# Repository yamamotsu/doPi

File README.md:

# doPi

"doPi" is Simple Raspberry Pi zero DAC Board.

## Feature

- DAC: PCM5102 by Texas Instruments
  - Sampling Rate: 384kHz Max(using up to 192kHz)
  - Number of bits of sample: 32-Bit
- Output: 3.5mm 3-pole jack
- Function: Next,Prev,Play/Stop, Volume +/-

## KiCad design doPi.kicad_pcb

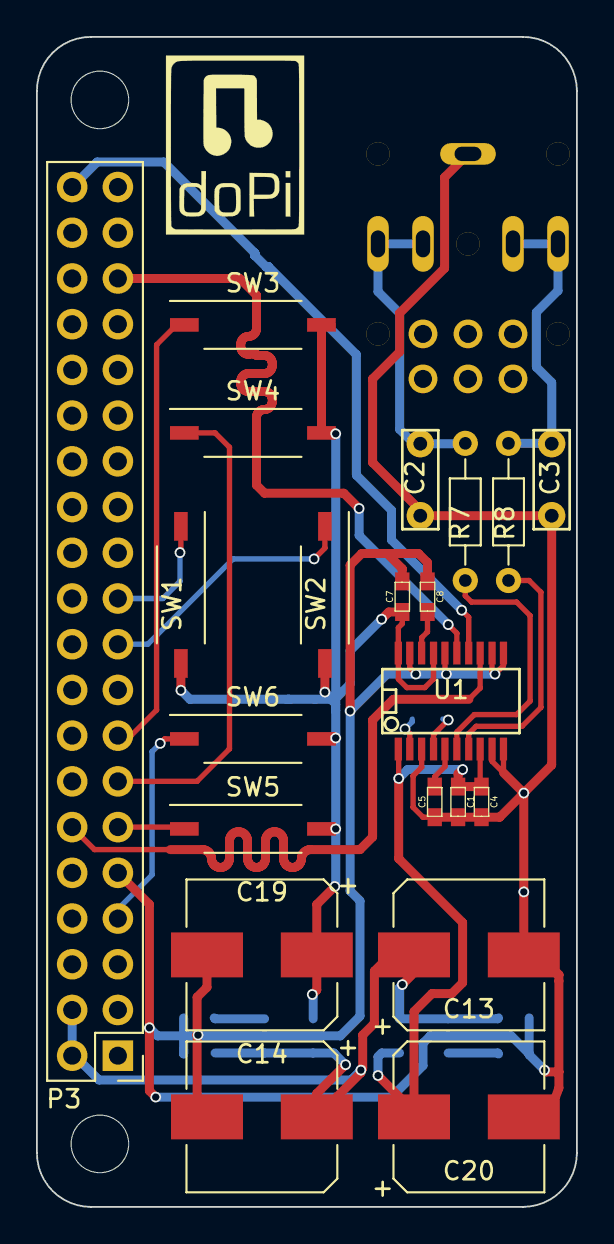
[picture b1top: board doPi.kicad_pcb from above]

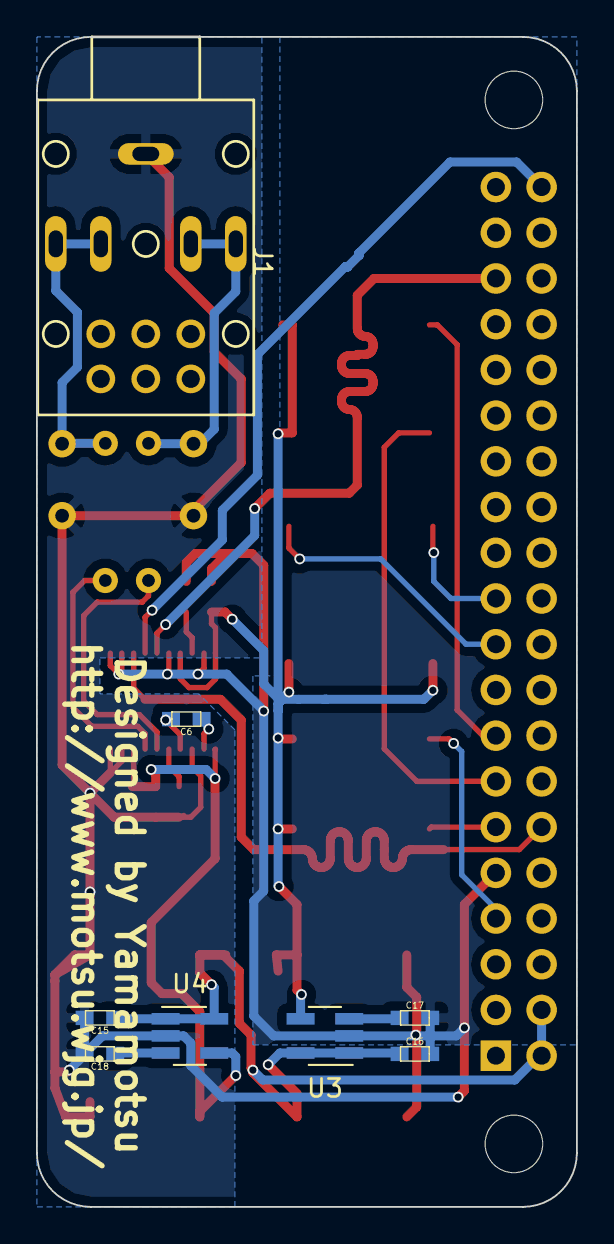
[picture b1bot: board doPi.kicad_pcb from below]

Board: 2 copper layers, 30.0 x 65.0 mm, 29 parts (8 on the bottom side), 23 nets.

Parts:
C1, C5, C6: 2.2uF; SMD_1608
C2, C3: 2200pF; Capacitors_ThroughHole_Film_L5.5mm_W2mm_P4mm
C4, C7, C8, C15, C16, C17, C18: 0.1uF; SMD_1608
C13, C14, C19, C20: 330uF; CP_Elec_8x6.5
J1: PJ_306B_JACK; PJ-306B_audio_jack
P3: ZERO_J8_HEADER; Pin_Header_Straight_2x20_Pitch2.54mm
R7, R8: 470; R_Axial_DIN0204_L3.6mm_D1.6mm_P7.62mm_Horizontal
SW1: SW_PREV; SW_DIP_x1_W7.62mm_Slide_Copal_CHS-B
SW2: SW_NEXT; SW_DIP_x1_W7.62mm_Slide_Copal_CHS-B
SW3: SW_VOL+; SW_DIP_x1_W7.62mm_Slide_Copal_CHS-B
SW4: SW_VOL-; SW_DIP_x1_W7.62mm_Slide_Copal_CHS-B
SW5: SW_PLAY/STOP; SW_DIP_x1_W7.62mm_Slide_Copal_CHS-B
SW6: SW_SHUFFLE; SW_DIP_x1_W7.62mm_Slide_Copal_CHS-B
U1: PCM5102; SSOP-20
U3, U4: NJM2863F; SOT-23-5_HandSoldering

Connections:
GND: C1.2, C2.1, C3.2, C4.2, C5.1, C7.2, C8.1, C13.2, C14.2, C15.2, C16.2, C17.2, C18.2, C19.2, C20.2, J1.1, P3.9, U1.3, U1.9, U1.10, U1.11, U1.12, U1.16, U1.19, U3.2, U4.2
unnamed: C2.2, J1.2, J1.3, R7.2
unnamed: C3.1, J1.4, J1.5, R8.2
unnamed: C5.2, U1.5
unnamed: C6.1, U1.2
unnamed: C6.2, U1.4
unnamed: C8.2, U1.18
unnamed: C13.1, C14.1, C15.1, C16.1, P3.2, P3.4, U3.1, U3.5, U4.1, U4.5
unnamed: C17.1, U3.3
unnamed: C18.1, U4.3
unnamed: P3.7, SW6.1
unnamed: P3.11, SW5.1
unnamed: P3.12, U1.13
unnamed: P3.13, SW4.1
unnamed: P3.15, SW3.1
unnamed: P3.19, SW2.1
unnamed: P3.21, SW1.1
unnamed: P3.35, U1.15
unnamed: P3.40, U1.14
unnamed: R7.1, U1.6
unnamed: R8.1, U1.7
VAA: C1.1, C4.1, C20.1, U1.1, U1.8, U4.4
VCC: C7.1, C19.1, SW1.2, SW2.2, SW3.2, SW4.2, SW5.2, SW6.2, U1.17, U1.20, U3.4

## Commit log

2018-05-16 readme added
